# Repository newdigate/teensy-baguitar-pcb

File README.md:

# teensy guitar audio sheild eurorack adapter and breakout pcb
printed circuit board design to integrate teensy microcontroller board, teensy guitar audio pro shield and eurorack.

# breakouts 
* st7735 oled display 
* digital io pins
* analog io pins
* 16 pin eurorack power header

# required hardware
* teensy 3.2 - 3.6: 
  * https://www.pjrc.com/store/teensy36.html
* teensy guitar audio shield 
  * https://www.tindie.com/products/Blackaddr/arduino-teensy-guitar-audio-shield/
* 128 x 128 ST7735 16-bit color display

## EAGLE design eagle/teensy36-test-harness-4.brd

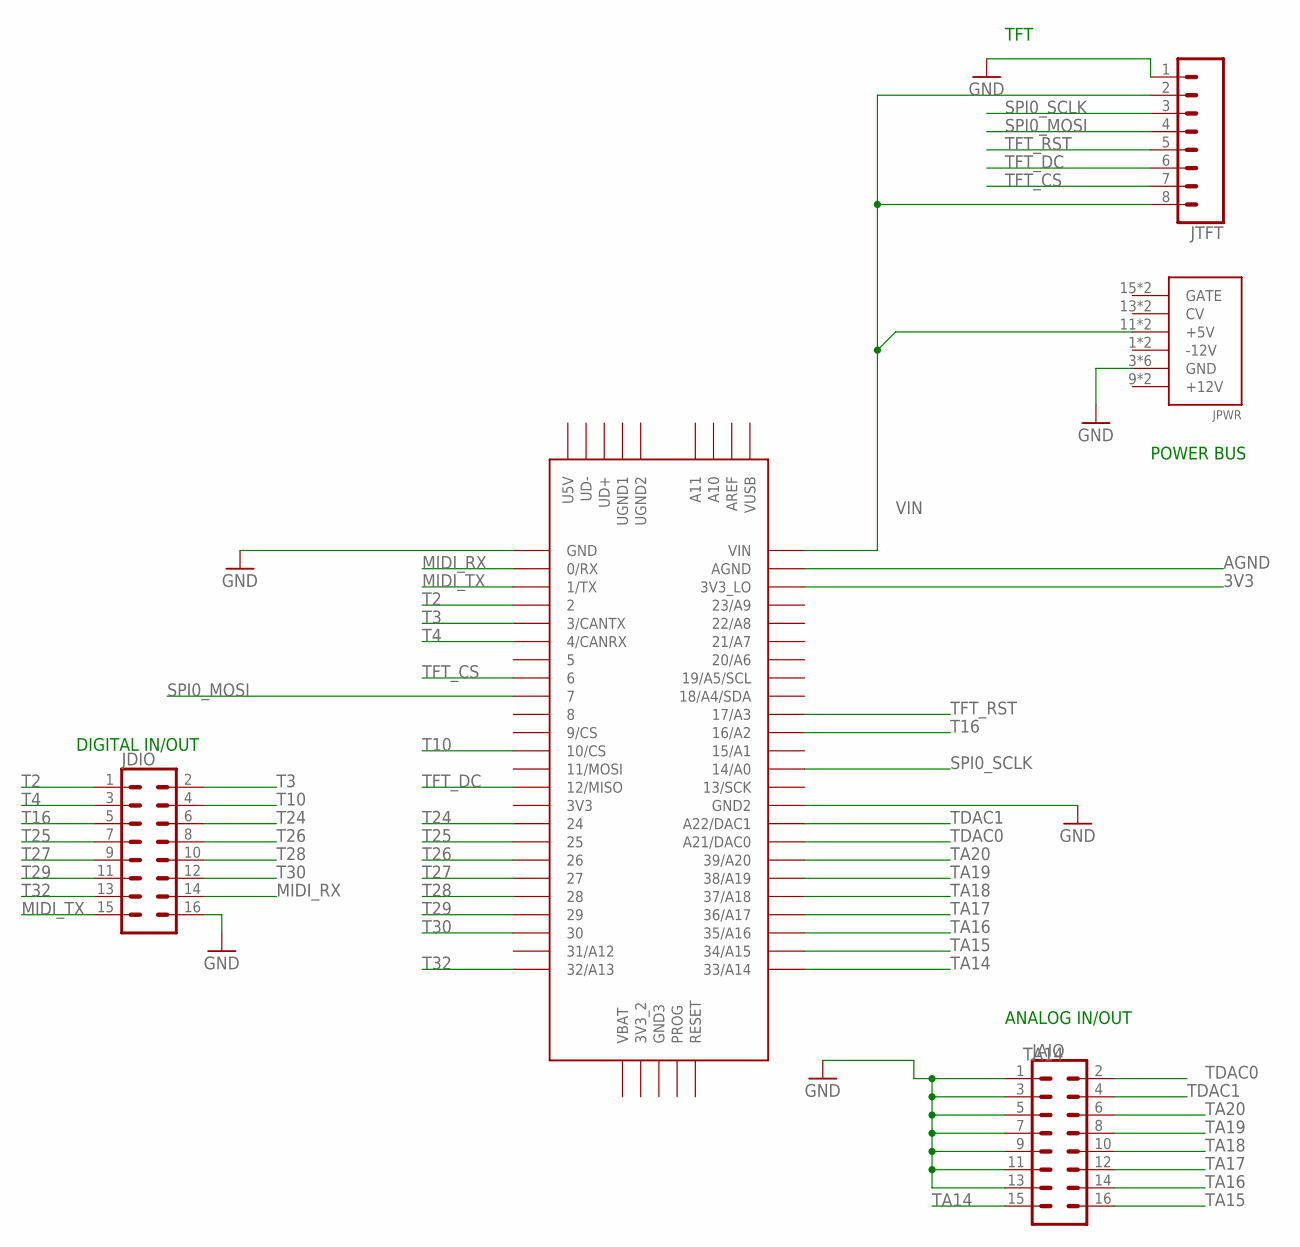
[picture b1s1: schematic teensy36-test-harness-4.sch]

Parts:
JAIO: CONN_08X2; 2X8
JDIO: CONN_08X2; 2X8
JPWR: POWER; POWER_16
JTFT: CONN_08"; 1X08
U$3: TEENSY_3.5/3.6

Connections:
3V3: U$3.3V3_LO
AGND: U$3.AGND
GND: JAIO.1, JAIO.3, JAIO.5, JAIO.7, JAIO.9, JAIO.11, JAIO.13, JDIO.16, JPWR.3 (GND), JPWR.4 (GND), JPWR.5 (GND), JPWR.6 (GND), JPWR.7 (GND), JPWR.8 (GND), JTFT.1, U$3.GND, U$3.GND2
MIDI_RX: JDIO.14, U$3.0/RX
MIDI_TX: JDIO.15, U$3.1/TX
SPI0_MOSI: JTFT.4, U$3.7
SPI0_SCLK: JTFT.3, U$3.14/A0
T2: JDIO.1, U$3.2
T3: JDIO.2, U$3.3/CANTX
T4: JDIO.3, U$3.4/CANRX
T10: JDIO.4, U$3.10/CS
T16: JDIO.5, U$3.16/A2
T24: JDIO.6, U$3.24
T25: JDIO.7, U$3.25
T26: JDIO.8, U$3.26
T27: JDIO.9, U$3.27
T28: JDIO.10, U$3.28
T29: JDIO.11, U$3.29
T30: JDIO.12, U$3.30
T32: JDIO.13, U$3.32/A13
TA14: JAIO.15, U$3.33/A14
TA15: JAIO.16, U$3.34/A15
TA16: JAIO.14, U$3.35/A16
TA17: JAIO.12, U$3.36/A17
TA18: JAIO.10, U$3.37/A18
TA19: JAIO.8, U$3.38/A19
TA20: JAIO.6, U$3.39/A20
TDAC0: JAIO.2, U$3.21/DAC0 (A21/DAC0)
TDAC1: JAIO.4, U$3.A22/DAC1
TFT_CS: JTFT.7, U$3.6
TFT_DC: JTFT.6, U$3.12/MISO
TFT_RST: JTFT.5, U$3.17/A3
VIN: JPWR.11 (+5V), JPWR.12 (+5V), JTFT.2, JTFT.8, U$3.VIN

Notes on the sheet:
DIGITAL IN/OUT
ANALOG IN/OUT
TFT
POWER BUS

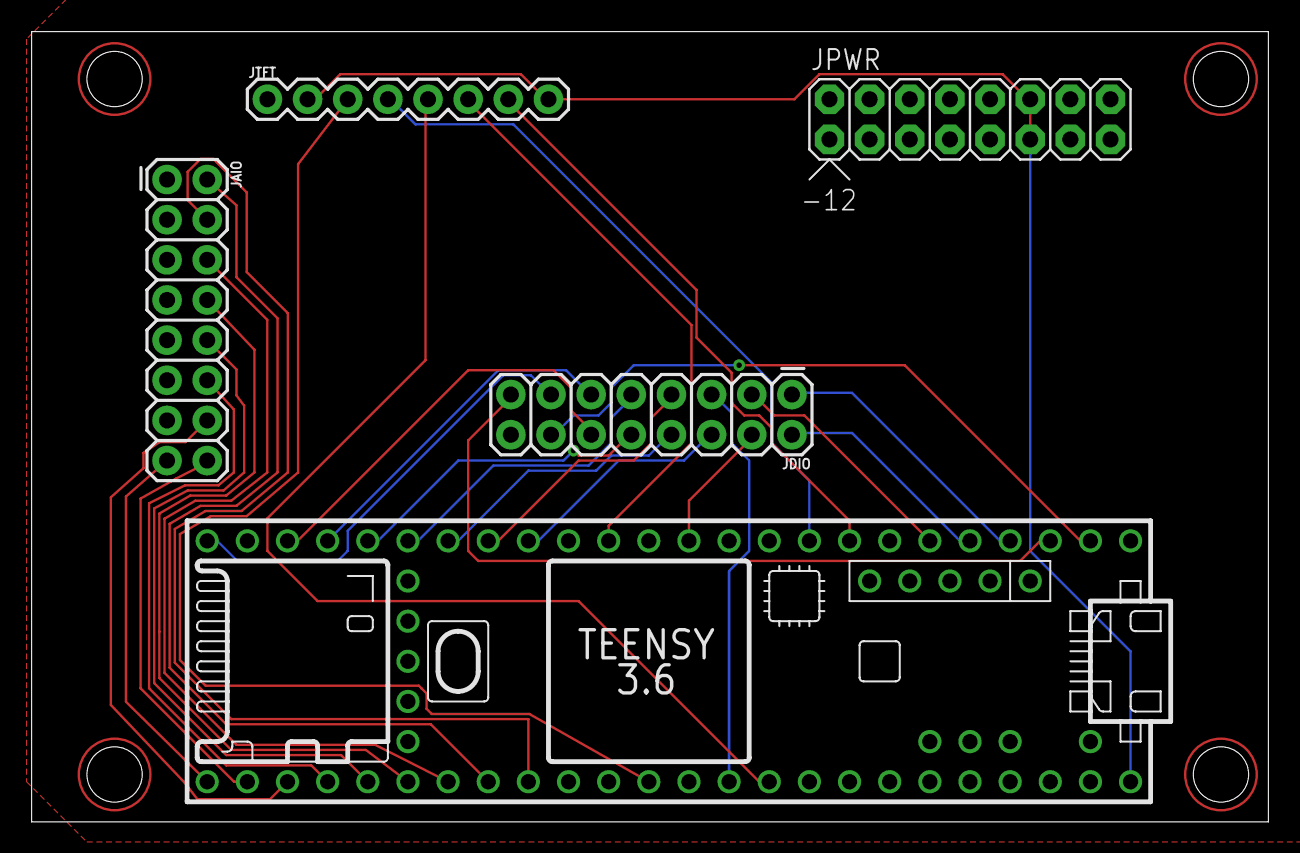
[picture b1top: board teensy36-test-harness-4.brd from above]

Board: 2 copper layers, 78.2 x 50.0 mm, 5 parts (0 on the bottom side), 31 nets.

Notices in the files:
parts and their libraries:
SparkFun-Connectors: Licensing: Creative Commons ShareAlike 4.0 International - https://creativecommons.org/licenses/by-sa/4.0
